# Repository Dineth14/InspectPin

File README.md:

# InspectPin AI

InspectPin is a wearable electronics-inspection assistant built around the XIAO
ESP32-S3 Sense. This repository contains the embedded firmware, local AI
backend, persistent product API, React dashboard, Flutter companion app and a
Windows virtual device.

The simulator demonstrates the complete mock PHOTO and ASK transport path; mock
output is labelled and is not camera recognition, speech recognition or
physical validation. See the [current audit](docs/CURRENT_STATE_AUDIT.md),
[acceptance report](docs/ACCEPTANCE_REPORT.md) and
[known limitations](docs/KNOWN_LIMITATIONS.md).

## System flow

```text
PHOTO → OV3660 JPEG → SD/offline queue → authenticated backend → vision result
ASK   → PDM WAV → SD/offline queue → STT → grounded answer → TTS → MAX98357A
                                ↓
                    web dashboard / Flutter app / report
```

Each visual question binds an explicit image/context ID. Provider prompts require
visible evidence and uncertainty and prohibit invented electrical measurements
or safety certification.

## Quick mock demonstration — Windows PowerShell

From the repository root:

```powershell
py -3.12 -m venv .venv
.\.venv\Scripts\python.exe -m pip install -r backend\requirements.txt -r backend\requirements-dev.txt
Copy-Item backend\.env.mock.example backend\.env
.\.venv\Scripts\python.exe backend\receiver.py
```

In a second terminal:

```powershell
.\.venv\Scripts\python.exe simulator\inspectpin_simulator.py bootstrap
.\.venv\Scripts\python.exe simulator\inspectpin_simulator.py scenario backend\tests\fixtures\synthetic_nameplate_a.jpg
```

Dashboard:

```powershell
Set-Location web
npm install
npm run dev
```

Open `http://127.0.0.1:5173`. For one-command container demonstration, run
`docker compose up --build` and open `http://127.0.0.1:8080`.

## Real models and physical device

Follow [INSTALLATION](docs/INSTALLATION.md) and
[MULTIMODAL_GUIDE](docs/MULTIMODAL_GUIDE.md) to install Whisper, Ollama/Qwen and
Piper, configure the laptop LAN address/token and upload the XIAO firmware.
Hardware-only acceptance is in [HARDWARE_VALIDATION](docs/HARDWARE_VALIDATION.md)
and [TESTING](docs/TESTING.md).

Historical bench evidence shows physical voice capture, backend processing and
audible playback have worked. Volume, clear-label camera recognition and the
reconciled Rev E electronics still require controlled acceptance. The final
hardware decision uses ASK on D2/GPIO3, PHOTO on PCF8574 P3 and the calibrated
battery divider on D5/GPIO6; MAX17043/MAX17048 are removed.

## Development checks

```powershell
.\.venv\Scripts\python.exe -m pytest -q
.\.venv\Scripts\python.exe -m ruff check backend simulator
.\.venv\Scripts\python.exe -m compileall -q backend simulator
.\.venv\Scripts\python.exe -m pip check
Set-Location web
npm run test
npm run build
```

The established mobile project is Flutter. See [MOBILE_APP](docs/MOBILE_APP.md).
The current machine does not have Flutter, so mobile build verification is
explicitly pending.

## Documentation

| Document | Purpose |
|---|---|
| [CURRENT_STATE_AUDIT](docs/CURRENT_STATE_AUDIT.md) | Verified, unverified and missing functionality |
| [ARCHITECTURE](docs/ARCHITECTURE.md) | Firmware/inference design and recovery |
| [API](docs/API.md) / [API_REFERENCE](docs/API_REFERENCE.md) | Product and embedded inference contracts |
| [DATABASE](docs/DATABASE.md) | Persistence model and production boundary |
| [AI_PIPELINE](docs/AI_PIPELINE.md) | Providers, grounding and failure handling |
| [DEVICE_PROTOCOL](docs/DEVICE_PROTOCOL.md) | Pairing, heartbeat, commands and uploads |
| [HARDWARE_PROFILES](docs/HARDWARE_PROFILES.md) | Development and Rev E candidate profiles |
| [LOCAL_SETUP_WINDOWS](docs/LOCAL_SETUP_WINDOWS.md) | Backend, web, simulator and mobile setup |
| [SECURITY_REVIEW](docs/SECURITY_REVIEW.md) | Controls and remaining trust limitations |
| [PROJECT_STATUS](docs/PROJECT_STATUS.md) | Historical implementation/bench evidence |
| [BRAND_GUIDELINES](docs/BRAND_GUIDELINES.md) | Logo, colour, typography and product voice |
| [DESIGN_SYSTEM](docs/DESIGN_SYSTEM.md) | Shared web/mobile tokens, components and states |
| [UI_REDESIGN](docs/UI_REDESIGN.md) | Premium redesign implementation and before/after |
| [ACCESSIBILITY_REVIEW](docs/ACCESSIBILITY_REVIEW.md) | Implemented accessibility and outstanding checks |
| [VISUAL_QA](docs/VISUAL_QA.md) | QA environment, viewport matrix and current blocker |

Do not commit `.env`, firmware `config.local.h`, device/Wi-Fi credentials,
provider keys, generated media or `.build/simulator-state.json`.

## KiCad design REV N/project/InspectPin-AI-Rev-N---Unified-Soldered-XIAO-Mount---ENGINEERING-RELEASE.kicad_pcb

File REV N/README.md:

# InspectPin_AI_Rev_N_-_Unified_Soldered_XIAO_Mount_-_ENGINEERING_RELEASE

Exported by PCBKit (https://pcbkit.io). The board is **complete**.

| Folder | What |
|---|---|
| `fabrication/` | what a fab and an assembly service need: `InspectPin_AI_Rev_N_-_Unified_Soldered_XIAO_Mount_-_ENGINEERING_RELEASE-fab.zip` to upload (Gerber X2 per layer, Excellon drill), `InspectPin_AI_Rev_N_-_Unified_Soldered_XIAO_Mount_-_ENGINEERING_RELEASE-BOM.csv` and `InspectPin_AI_Rev_N_-_Unified_Soldered_XIAO_Mount_-_ENGINEERING_RELEASE-CPL.csv` for assembly, `README.md` with what the order form asks |
| `project/` | the project: its files in `.pcbkit/` (open the folder in PCBKit to keep working) and the board exported as a KiCad project (open the `.kicad_pro` in KiCad 8 or later) |
| `schematic/` | the schematic as PDF (a page per sheet, printable at 1:1) and SVG |

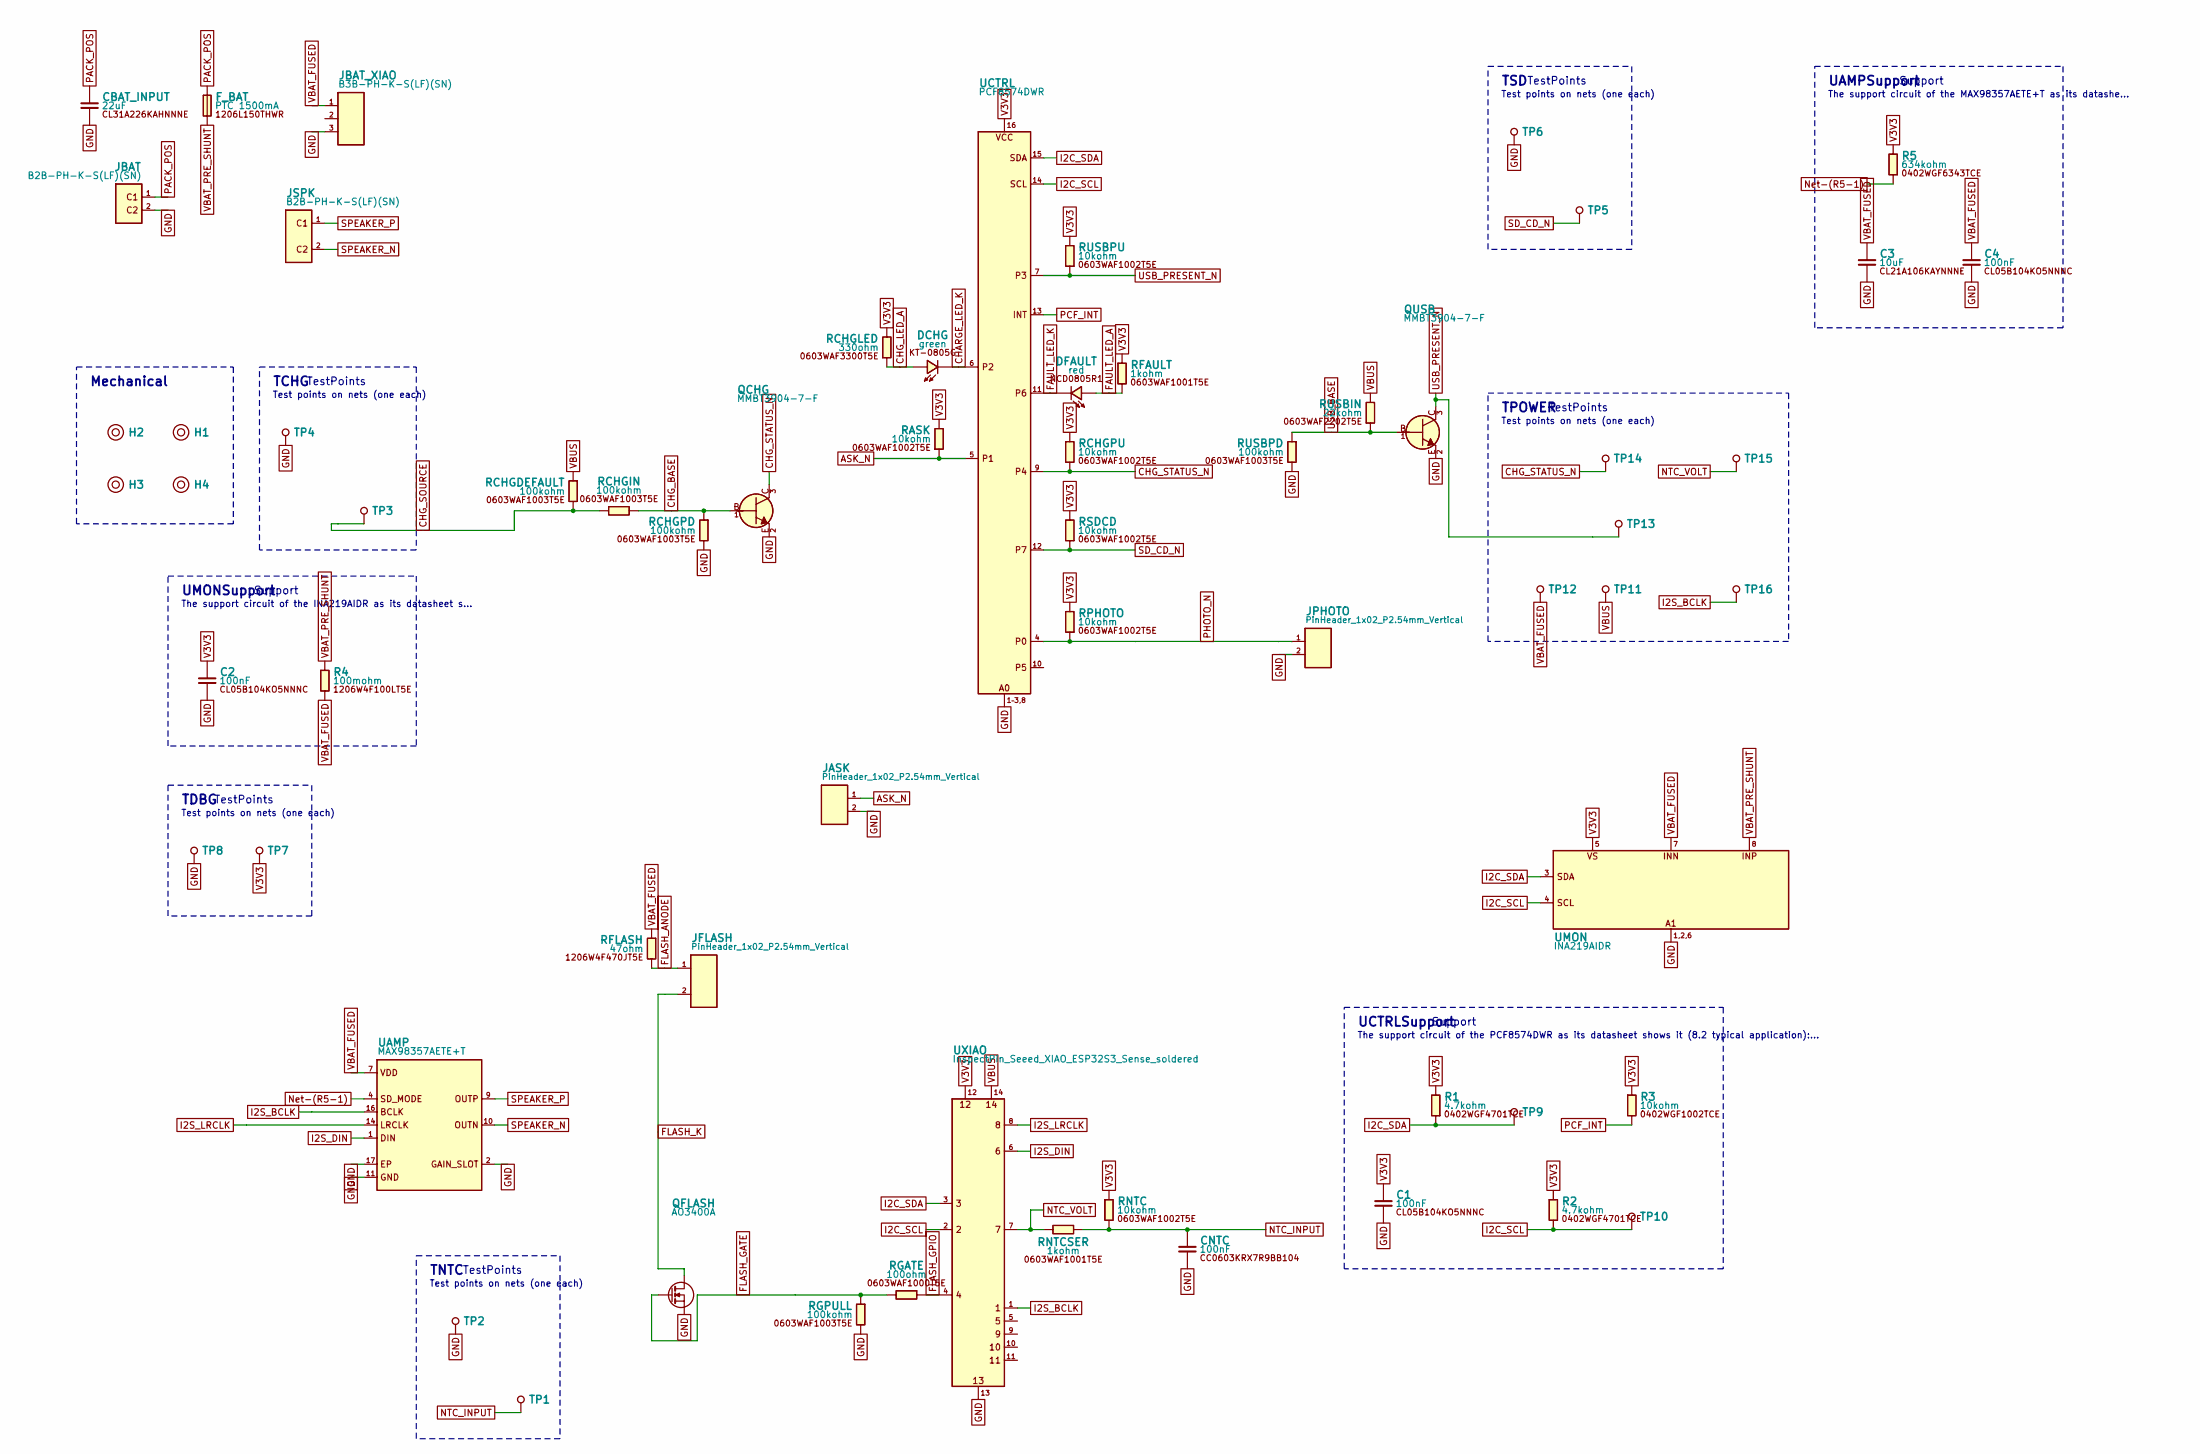
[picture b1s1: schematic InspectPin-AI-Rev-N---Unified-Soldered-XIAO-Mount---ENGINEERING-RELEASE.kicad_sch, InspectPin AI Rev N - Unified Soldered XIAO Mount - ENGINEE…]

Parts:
C1, C2, C4: 100nF; C_0402_1005Metric; MPN CL05B104KO5NNNC; LCSC Part # C1525
C3: 10uF; C_0805_2012Metric; MPN CL21A106KAYNNNE; LCSC Part # C15850
CBAT_INPUT: 22uF; C_1206_3216Metric; MPN CL31A226KAHNNNE; LCSC Part # C12891
CNTC: 100nF; C_0603_1608Metric; MPN CC0603KRX7R9BB104; LCSC Part # C14663
DCHG: green; LED_0805_2012Metric; MPN KT-0805G; LCSC Part # C2297
DFAULT: red; LED_0805_2012Metric; MPN NCD0805R1; LCSC Part # C84256
F_BAT: PTC 1500mA; Fuse_1206_3216Metric; MPN 1206L150THWR; LCSC Part # C118413
H1, H2, H3, H4: MountingHole_2.2mm_M2
JASK: PinHeader_1x02_P2.54mm_Vertical; MPN MTP125-1102S1; LCSC Part # C358684
JBAT: B2B-PH-K-S(LF)(SN); JST_PH_B2B-PH-K_1x02_P2.00mm_Vertical; MPN B2B-PH-K-S(LF)(SN); LCSC Part # C131337
JBAT_XIAO: B3B-PH-K-S(LF)(SN); Conn_WireToBoard_1x03_P2.00mm_THT_Vertical; MPN B3B-PH-K-S(LF)(SN); LCSC Part # C131339
JFLASH: PinHeader_1x02_P2.54mm_Vertical; MPN MTP125-1102S1; LCSC Part # C358684
JPHOTO: PinHeader_1x02_P2.54mm_Vertical; MPN MTP125-1102S1; LCSC Part # C358684
JSPK: B2B-PH-K-S(LF)(SN); JST_PH_B2B-PH-K_1x02_P2.00mm_Vertical; MPN B2B-PH-K-S(LF)(SN); LCSC Part # C131337
QCHG: MMBT3904-7-F; SOT-23; MPN MMBT3904-7-F; LCSC Part # C94514
QFLASH: AO3400A; SOT-23; MPN AO3400A; LCSC Part # C20917
QUSB: MMBT3904-7-F; SOT-23; MPN MMBT3904-7-F; LCSC Part # C94514
R1, R2: 4.7kohm; R_0402_1005Metric; MPN 0402WGF4701TCE; LCSC Part # C25900
R3: 10kohm; R_0402_1005Metric; MPN 0402WGF1002TCE; LCSC Part # C25744
R4: 100mohm; R_1206_3216Metric; MPN 1206W4F100LT5E; LCSC Part # C25334
R5: 634kohm; R_0402_1005Metric; MPN 0402WGF6343TCE; LCSC Part # C270588
RASK: 10kohm; R_0603_1608Metric; MPN 0603WAF1002T5E; LCSC Part # C25804
RCHGDEFAULT: 100kohm; R_0603_1608Metric; MPN 0603WAF1003T5E; LCSC Part # C25803
RCHGIN: 100kohm; R_0603_1608Metric; MPN 0603WAF1003T5E; LCSC Part # C25803
RCHGLED: 330ohm; R_0603_1608Metric; MPN 0603WAF3300T5E; LCSC Part # C23138
RCHGPD: 100kohm; R_0603_1608Metric; MPN 0603WAF1003T5E; LCSC Part # C25803
RCHGPU: 10kohm; R_0603_1608Metric; MPN 0603WAF1002T5E; LCSC Part # C25804
RFAULT: 1kohm; R_0603_1608Metric; MPN 0603WAF1001T5E; LCSC Part # C21190
RFLASH: 47ohm; R_1206_3216Metric; MPN 1206W4F470JT5E; LCSC Part # C17969
RGATE: 100ohm; R_0603_1608Metric; MPN 0603WAF1000T5E; LCSC Part # C22775
RGPULL: 100kohm; R_0603_1608Metric; MPN 0603WAF1003T5E; LCSC Part # C25803
RNTC: 10kohm; R_0603_1608Metric; MPN 0603WAF1002T5E; LCSC Part # C25804
RNTCSER: 1kohm; R_0603_1608Metric; MPN 0603WAF1001T5E; LCSC Part # C21190
RPHOTO: 10kohm; R_0603_1608Metric; MPN 0603WAF1002T5E; LCSC Part # C25804
RSDCD: 10kohm; R_0603_1608Metric; MPN 0603WAF1002T5E; LCSC Part # C25804
RUSBIN: 22kohm; R_0603_1608Metric; MPN 0603WAF2202T5E; LCSC Part # C31850
RUSBPD: 100kohm; R_0603_1608Metric; MPN 0603WAF1003T5E; LCSC Part # C25803
RUSBPU: 10kohm; R_0603_1608Metric; MPN 0603WAF1002T5E; LCSC Part # C25804
TP1, TP2, TP3, TP4, TP5, TP6: TestPoint_Round_D1.8mm
TP7, TP8, TP9, TP10, TP11, TP12, TP13, TP14, TP15, TP16: TestPoint_Round_D1.5mm
UAMP: MAX98357AETE+T; QFN-16-1EP_3x3mm_P0.5mm_EP1.1x1.1mm; MPN MAX98357AETE+T; LCSC Part # C910544
UCTRL: PCF8574DWR; SOIC-16W_7.5x10.3mm_P1.27mm; MPN PCF8574DWR; LCSC Part # C2652271
UMON: INA219AIDR; SOIC-8_3.9x4.9mm_P1.27mm; MPN INA219AIDR; LCSC Part # C138706
UXIAO: InspectPin_Seeed_XIAO_ESP32S3_Sense_soldered

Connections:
ASK_N: JASK.1, RASK.1 (a), UCTRL.5 (P1)
CHARGE_LED_K: DCHG.1 (K), UCTRL.6 (P2)
CHG_BASE: QCHG.1 (B), RCHGIN.2 (b), RCHGPD.1 (a)
CHG_LED_A: DCHG.2 (A), RCHGLED.1 (a)
CHG_SOURCE: RCHGDEFAULT.2 (b), RCHGIN.1 (a), TP3.1
CHG_STATUS_N: QCHG.3 (C), RCHGPU.2 (b), TP14.1, UCTRL.9 (P4)
FAULT_LED_A: DFAULT.2 (A), RFAULT.2 (b)
FAULT_LED_K: DFAULT.1 (K), UCTRL.11 (P6)
FLASH_ANODE: JFLASH.1, RFLASH.2 (b)
FLASH_GATE: QFLASH.1 (G), RGATE.2 (b), RGPULL.1 (a)
FLASH_GPIO: RGATE.1 (a), UXIAO.4
FLASH_K: JFLASH.2, QFLASH.3 (D)
GND: C1.2 (b), C2.2 (b), C3.2 (b), C4.2 (b), CBAT_INPUT.2 (b), CNTC.2 (b), JASK.2, JBAT.2 (C2), JBAT_XIAO.3, JPHOTO.2, QCHG.2 (E), QFLASH.2 (S), QUSB.2 (E), RCHGPD.2 (b), RGPULL.2 (b), RUSBPD.2 (b), TP2.1, TP4.1, TP6.1, TP8.1, UAMP.2 (GAIN_SLOT), UAMP.3 (GND), UAMP.11 (GND), UAMP.15 (GND), UAMP.17 (EP), UCTRL.1 (A0), UCTRL.2 (A1), UCTRL.3 (A2), UCTRL.8 (GND), UMON.1 (A1), UMON.2 (A0), UMON.6 (GND), UXIAO.13
I2C_SCL: R2.2 (b), TP10.1, UCTRL.14 (SCL), UMON.4 (SCL), UXIAO.2
I2C_SDA: R1.1 (a), TP9.1, UCTRL.15 (SDA), UMON.3 (SDA), UXIAO.3
I2S_BCLK: TP16.1, UAMP.16 (BCLK), UXIAO.1
I2S_DIN: UAMP.1 (DIN), UXIAO.6
I2S_LRCLK: UAMP.14 (LRCLK), UXIAO.8
NTC_INPUT: CNTC.1 (a), RNTC.2 (b), RNTCSER.1 (a), TP1.1
NTC_VOLT: RNTCSER.2 (b), TP15.1, UXIAO.7
unnamed: R5.1 (a), UAMP.4 (SD_MODE)
PACK_POS: CBAT_INPUT.1 (a), F_BAT.1 (a), JBAT.1 (C1)
PCF_INT: R3.2 (b), UCTRL.13 (INT)
PHOTO_N: JPHOTO.1, RPHOTO.1 (a), UCTRL.4 (P0)
SD_CD_N: RSDCD.1 (a), TP5.1, UCTRL.12 (P7)
SPEAKER_N: JSPK.2 (C2), UAMP.10 (OUTN)
SPEAKER_P: JSPK.1 (C1), UAMP.9 (OUTP)
USB_BASE: QUSB.1 (B), RUSBIN.1 (a), RUSBPD.1 (a)
USB_PRESENT_N: QUSB.3 (C), RUSBPU.1 (a), TP13.1, UCTRL.7 (P3)
V3V3: C1.1 (a), C2.1 (a), R1.2 (b), R2.1 (a), R3.1 (a), R5.2 (b), RASK.2 (b), RCHGLED.2 (b), RCHGPU.1 (a), RFAULT.1 (a), RNTC.1 (a), RPHOTO.2 (b), RSDCD.2 (b), RUSBPU.2 (b), TP7.1, UCTRL.16 (VCC), UMON.5 (VS), UXIAO.12
VBAT_FUSED: C3.1 (a), C4.1 (a), JBAT_XIAO.1, R4.2 (b), RFLASH.1 (a), TP12.1, UAMP.7 (VDD), UAMP.8 (VDD), UMON.7 (INN)
VBAT_PRE_SHUNT: F_BAT.2 (b), R4.1 (a), UMON.8 (INP)
VBUS: RCHGDEFAULT.1 (a), RUSBIN.2 (b), TP11.1, UXIAO.14

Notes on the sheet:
UMONSupport
Support
The support circuit of the INA219AIDR as its datasheet s…
UCTRLSupport
The support circuit of the PCF8574DWR as its datasheet shows it (8.2 typical application):…
UAMPSupport
The support circuit of the MAX98357AETE+T as its datashe…
TNTC
TestPoints
Test points on nets (one each)
TCHG
TSD
TDBG
TPOWER
Mechanical

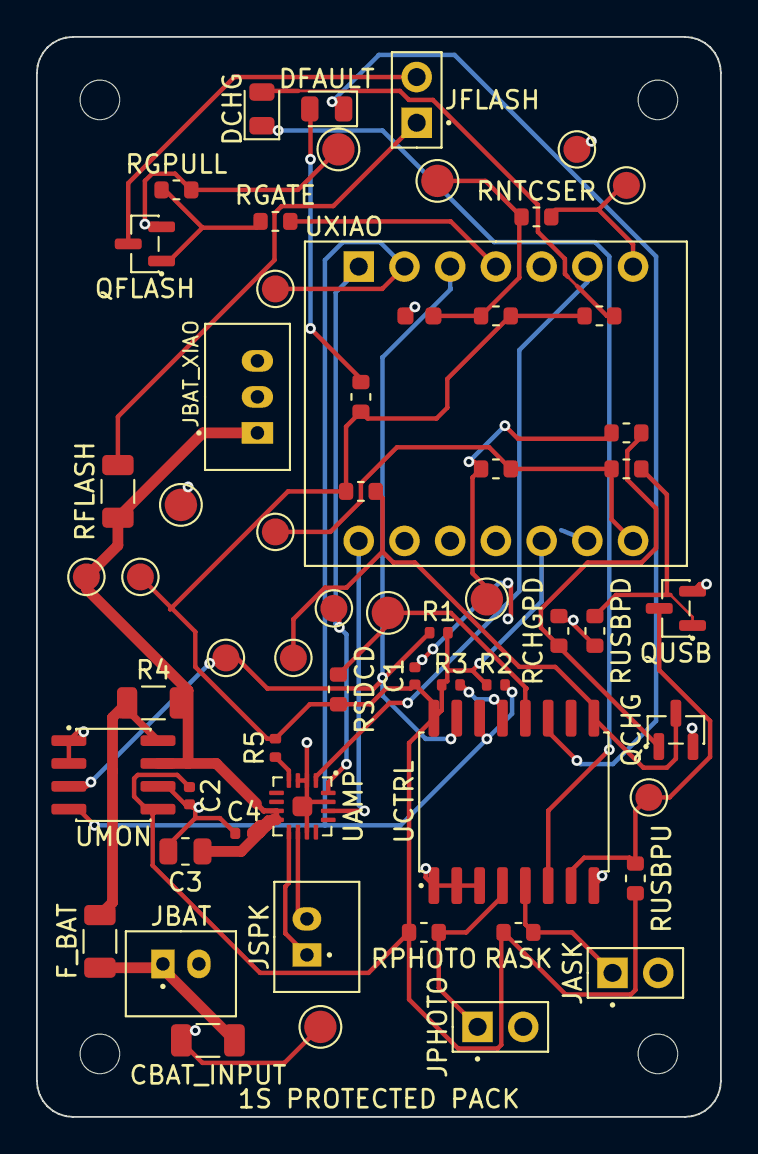
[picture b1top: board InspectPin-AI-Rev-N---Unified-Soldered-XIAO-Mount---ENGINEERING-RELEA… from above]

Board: 2 copper layers, 38.0 x 60.0 mm, 64 parts (0 on the bottom side), 33 nets.

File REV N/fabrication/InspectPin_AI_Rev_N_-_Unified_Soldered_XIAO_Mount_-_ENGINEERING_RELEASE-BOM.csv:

Comment,Designator,Footprint,LCSC Part #,Quantity
100nF,"C1,C2,C4",C_0402_1005Metric,C1525,3
10uF,C3,C_0805_2012Metric,C15850,1
22uF,CBAT_INPUT,C_1206_3216Metric,C12891,1
100nF,CNTC,C_0603_1608Metric,C14663,1
green,DCHG,LED_0805_2012Metric,C2297,1
red,DFAULT,LED_0805_2012Metric,C84256,1
PTC 1500mA,F_BAT,Fuse_1206_3216Metric,C118413,1
MTP125-1102S1,"JASK,JFLASH,JPHOTO",PinHeader_1x02_P2.54mm_Vertical,C358684,3
B2B-PH-K-S(LF)(SN),"JBAT,JSPK",JST_PH_B2B-PH-K_1x02_P2.00mm_Vertical,C131337,2
B3B-PH-K-S(LF)(SN),JBAT_XIAO,Conn_WireToBoard_1x03_P2.00mm_THT_Vertical,C131339,1
MMBT3904-7-F,"QCHG,QUSB",SOT-23,C94514,2
AO3400A,QFLASH,SOT-23,C20917,1
4.7kohm,"R1,R2",R_0402_1005Metric,C25900,2
10kohm,R3,R_0402_1005Metric,C25744,1
100mohm,R4,R_1206_3216Metric,C25334,1
634kohm,R5,R_0402_1005Metric,C270588,1
10kohm,"RASK,RCHGPU,RNTC,RPHOTO,RSDCD,RUSBPU",R_0603_1608Metric,C25804,6
100kohm,"RCHGDEFAULT,RCHGIN,RCHGPD,RGPULL,RUSBPD",R_0603_1608Metric,C25803,5
330ohm,RCHGLED,R_0603_1608Metric,C23138,1
1kohm,"RFAULT,RNTCSER",R_0603_1608Metric,C21190,2
47ohm,RFLASH,R_1206_3216Metric,C17969,1
100ohm,RGATE,R_0603_1608Metric,C22775,1
22kohm,RUSBIN,R_0603_1608Metric,C31850,1
MAX98357AETE+T,UAMP,QFN-16-1EP_3x3mm_P0.5mm_EP1.1x1.1mm,C910544,1
PCF8574DWR,UCTRL,SOIC-16W_7.5x10.3mm_P1.27mm,C2652271,1
INA219AIDR,UMON,SOIC-8_3.9x4.9mm_P1.27mm,C138706,1

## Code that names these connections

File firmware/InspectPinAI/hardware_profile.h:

#pragma once
#include <stdint.h>

// Reconciled Rev E specification. Physical enabling remains gated until the
// missing KiCad source is reviewed and the assembled nets are continuity-tested.
namespace HardwareProfile {
#if defined(IP_USE_REV_N_CONFIG)
// Rev N values reconciled against the KiCad PCB/netlist and PCBKit source
// supplied in REV N/ on 2026-11-05. Quasi-bidirectional inputs stay HIGH.
constexpr int askButtonGpio = -1;      // ASK is PCF8574 P1. GPIO3 is reserved.
constexpr int pcfInterruptGpio = -1;   // No interrupt GPIO was specified; polling only.
constexpr int batteryAdcGpio = -1;     // INA219 replaces the Rev E divider.
constexpr int pcfSdaGpio = 5;
constexpr int pcfSclGpio = 6;
constexpr int ntcGpio = 1;
constexpr int flashlightGpio = 4;
constexpr int speakerDataGpio = 2;
constexpr int speakerBclkGpio = 43;
constexpr int speakerLrclkGpio = 44;
constexpr int hapticGpio = -1;
constexpr int reservedGpio = 3;
constexpr uint8_t pcfAddress = 0x20;
constexpr uint8_t ina219Address = 0x40;

constexpr uint8_t pcfPhotoButton = 0;  // PHOTO_N, active low.
constexpr uint8_t pcfAskButton = 1;    // ASK_N, active low.
constexpr uint8_t pcfStatusLed = 2;    // CHARGE_LED_K, active-low sink.
constexpr uint8_t pcfUsbPresentN = 3;  // USB_PRESENT_N, low when USB is inserted.
constexpr uint8_t pcfChargeN = 4;      // CHG_STATUS_N: HIGH=charging only with verified NCHG tap.
constexpr uint8_t pcfSpare = 5;        // Unconnected in KiCad.
constexpr uint8_t pcfFaultLed = 6;     // FAULT_LED_K, active-low sink.
constexpr uint8_t pcfCardDetectN = 7;  // SD_CD_N, low when optional switch closes.
constexpr uint8_t pcfChargeFullN = pcfChargeN; // Compatibility only; not a full signal.
constexpr uint8_t pcfChargeValidN = pcfSpare;
constexpr uint8_t pcfFlashlight = pcfSpare;
constexpr uint8_t pcfVibration = pcfSpare;
#else
constexpr int askButtonGpio = 3;       // XIAO D2; strap precaution applies.
constexpr int pcfInterruptGpio = 5;    // XIAO D4; RTC GPIO, active-low INT.
constexpr int batteryAdcGpio = 6;      // XIAO D5; 100k/100k divider midpoint.
constexpr int pcfSdaGpio = 43;         // XIAO D6.
constexpr int pcfSclGpio = 44;         // XIAO D7.
constexpr uint8_t pcfAddress = 0x20;   // PCF8574 A2:A0 tied low.

constexpr uint8_t pcfFlashlight = 0;   // Active-low before fail-safe inverter.
constexpr uint8_t pcfVibration = 1;    // Active-low before fail-safe inverter.
constexpr uint8_t pcfPhotoButton = 3;  // Button to GND; HIGH when released.
constexpr uint8_t pcfUsbPresentN = 4;  // Decoder open drain: LOW = USB present.
constexpr uint8_t pcfChargeFullN = 5;  // Decoder open drain: LOW = full.
constexpr uint8_t pcfChargeValidN = 6; // Decoder open drain: LOW = status valid.
constexpr uint8_t pcfSpare = 7;
constexpr uint8_t pcfAskButton = 2;
constexpr uint8_t pcfStatusLed = 2;
constexpr uint8_t pcfFaultLed = 7;
constexpr uint8_t pcfChargeN = 5;
constexpr uint8_t pcfCardDetectN = 7;
constexpr uint8_t ina219Address = 0x40;
constexpr int ntcGpio = -1;
constexpr int flashlightGpio = 43;
constexpr int speakerDataGpio = 4;
constexpr int speakerBclkGpio = 1;
constexpr int speakerLrclkGpio = 2;
constexpr int hapticGpio = 44;
constexpr int reservedGpio = -1;
#endif

#if !defined(IP_USE_REV_N_CONFIG)
static_assert(askButtonGpio != batteryAdcGpio, "ASK and battery ADC conflict");
static_assert(pcfInterruptGpio != batteryAdcGpio, "PCF INT and battery ADC conflict");
#endif
static_assert(pcfSdaGpio != pcfSclGpio, "I2C SDA/SCL conflict");
}
